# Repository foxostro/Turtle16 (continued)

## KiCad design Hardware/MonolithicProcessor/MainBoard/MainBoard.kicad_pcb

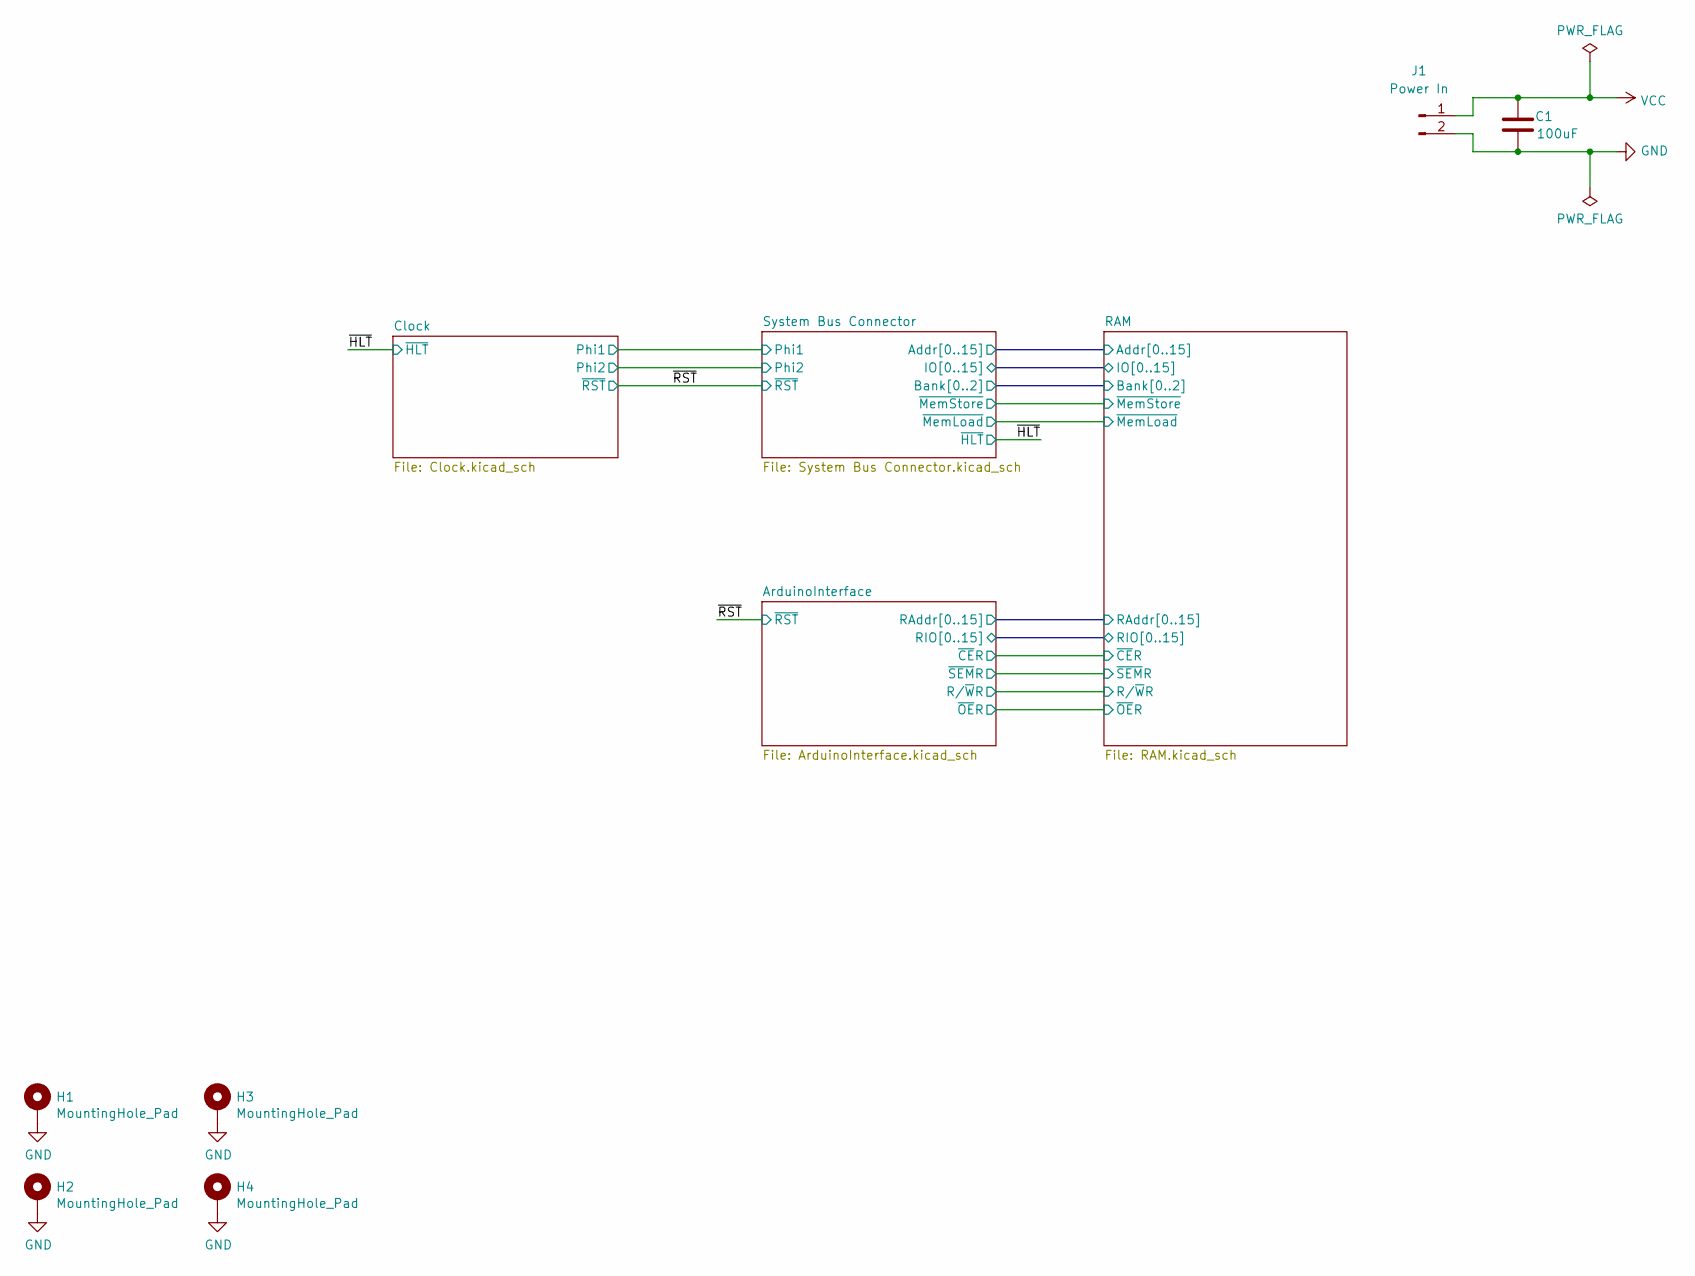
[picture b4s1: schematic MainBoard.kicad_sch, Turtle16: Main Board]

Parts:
C1: 100uF; C_1206_3216Metric; Manufacturer# AMK316ABJ107ML-T; Mouser# 963-AMK316ABJ107ML-T
H1, H2, H3, H4: MountingHole_Pad; MountingHole_3.2mm_M3_Pad
J1: Power In; 172448-0002; Manufacturer# 172448-0002; Mouser# 538-172448-0002

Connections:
GND: C1.2, H1.1, H2.1, H3.1, H4.1, J1.2; also elsewhere on the board
VCC: C1.1, J1.1; also elsewhere on the board

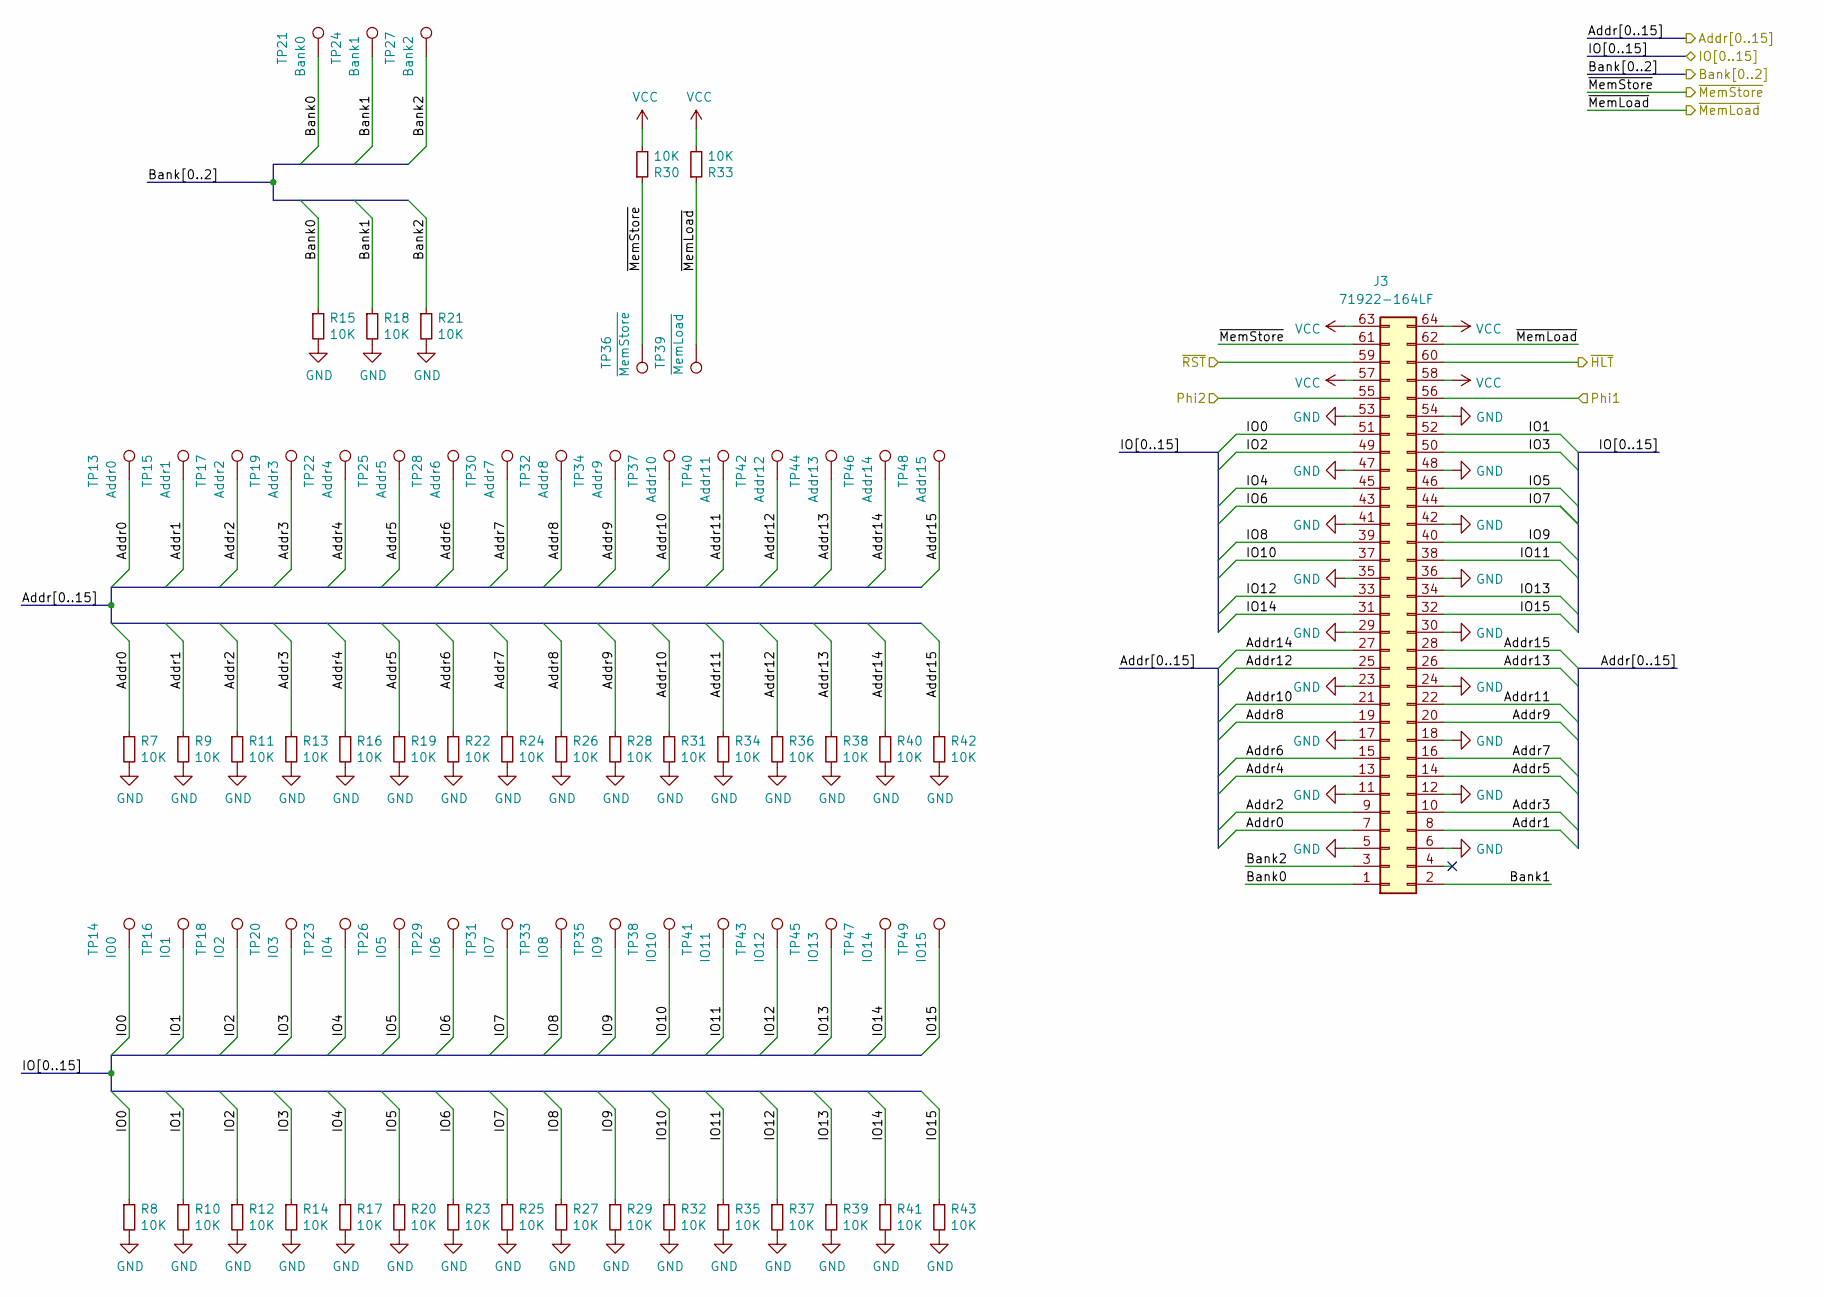
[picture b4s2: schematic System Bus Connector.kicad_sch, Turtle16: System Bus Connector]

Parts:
J3: 71922-164LF; IDC-Header_2x32_P2.54mm_Horizontal; Manufacturer# 71922-164LF; Mouser# 649-71922-164LF
R7, R8, R9, R10, R11, R12, R13, R14, R15, R16, R17, R18, R19, R20, R21, R22, R23, R24, R25, R26, R27, R28, R29, R30, R31, R32, R33, R34, R35, R36, R37, R38, R39, R40, R41, R42, R43: 10K; R_0603_1608Metric; Manufacturer# CR0603-FX-1002ELF; Mouser# 652-CR0603FX-1002ELF
TP13: Addr0; TestPoint_Pad_D1.0mm
TP14: IO0; TestPoint_Pad_D1.0mm
TP15: Addr1; TestPoint_Pad_D1.0mm
TP16: IO1; TestPoint_Pad_D1.0mm
TP17: Addr2; TestPoint_Pad_D1.0mm
TP18: IO2; TestPoint_Pad_D1.0mm
TP19: Addr3; TestPoint_Pad_D1.0mm
TP20: IO3; TestPoint_Pad_D1.0mm
TP21: Bank0; TestPoint_Pad_D1.0mm
TP22: Addr4; TestPoint_Pad_D1.0mm
TP23: IO4; TestPoint_Pad_D1.0mm
TP24: Bank1; TestPoint_Pad_D1.0mm
TP25: Addr5; TestPoint_Pad_D1.0mm
TP26: IO5; TestPoint_Pad_D1.0mm
TP27: Bank2; TestPoint_Pad_D1.0mm
TP28: Addr6; TestPoint_Pad_D1.0mm
TP29: IO6; TestPoint_Pad_D1.0mm
TP30: Addr7; TestPoint_Pad_D1.0mm
TP31: IO7; TestPoint_Pad_D1.0mm
TP32: Addr8; TestPoint_Pad_D1.0mm
TP33: IO8; TestPoint_Pad_D1.0mm
TP34: Addr9; TestPoint_Pad_D1.0mm
TP35: IO9; TestPoint_Pad_D1.0mm
TP36: ~{MemStore}; TestPoint_Pad_D1.0mm
TP37: Addr10; TestPoint_Pad_D1.0mm
TP38: IO10; TestPoint_Pad_D1.0mm
TP39: ~{MemLoad}; TestPoint_Pad_D1.0mm
TP40: Addr11; TestPoint_Pad_D1.0mm
TP41: IO11; TestPoint_Pad_D1.0mm
TP42: Addr12; TestPoint_Pad_D1.0mm
TP43: IO12; TestPoint_Pad_D1.0mm
TP44: Addr13; TestPoint_Pad_D1.0mm
TP45: IO13; TestPoint_Pad_D1.0mm
TP46: Addr14; TestPoint_Pad_D1.0mm
TP47: IO14; TestPoint_Pad_D1.0mm
TP48: Addr15; TestPoint_Pad_D1.0mm
TP49: IO15; TestPoint_Pad_D1.0mm

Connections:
/Clock/Phi1: J3.56; also elsewhere on the board
/Clock/Phi2: J3.55; also elsewhere on the board
/RAM/Addr0: J3.7, R7.1, TP13.1; also elsewhere on the board
/RAM/Addr1: J3.8, R9.1, TP15.1; also elsewhere on the board
/RAM/Addr2: J3.9, R11.1, TP17.1; also elsewhere on the board
/RAM/Addr3: J3.10, R13.1, TP19.1; also elsewhere on the board
/RAM/Addr4: J3.13, R16.1, TP22.1; also elsewhere on the board
/RAM/Addr5: J3.14, R19.1, TP25.1; also elsewhere on the board
/RAM/Addr6: J3.15, R22.1, TP28.1; also elsewhere on the board
/RAM/Addr7: J3.16, R24.1, TP30.1; also elsewhere on the board
/RAM/Addr8: J3.19, R26.1, TP32.1; also elsewhere on the board
/RAM/Addr9: J3.20, R28.1, TP34.1; also elsewhere on the board
/RAM/Addr10: J3.21, R31.1, TP37.1; also elsewhere on the board
/RAM/Addr11: J3.22, R34.1, TP40.1; also elsewhere on the board
/RAM/Addr12: J3.25, R36.1, TP42.1; also elsewhere on the board
/RAM/Addr13: J3.26, R38.1, TP44.1; also elsewhere on the board
/RAM/Addr14: J3.27, R40.1, TP46.1; also elsewhere on the board
/RAM/Addr15: J3.28, R42.1, TP48.1; also elsewhere on the board
/RAM/Bank0: J3.1, R15.1, TP21.1; also elsewhere on the board
/RAM/Bank1: J3.2, R18.1, TP24.1; also elsewhere on the board
/RAM/Bank2: J3.3, R21.1, TP27.1; also elsewhere on the board
/RAM/IO0: J3.51, R8.1, TP14.1; also elsewhere on the board
/RAM/IO1: J3.52, R10.1, TP16.1; also elsewhere on the board
/RAM/IO2: J3.49, R12.1, TP18.1; also elsewhere on the board
/RAM/IO3: J3.50, R14.1, TP20.1; also elsewhere on the board
/RAM/IO4: J3.45, R17.1, TP23.1; also elsewhere on the board
/RAM/IO5: J3.46, R20.1, TP26.1; also elsewhere on the board
/RAM/IO6: J3.43, R23.1, TP29.1; also elsewhere on the board
/RAM/IO7: J3.44, R25.1, TP31.1; also elsewhere on the board
/RAM/IO8: J3.39, R27.1, TP33.1; also elsewhere on the board
/RAM/IO9: J3.40, R29.1, TP35.1; also elsewhere on the board
/RAM/IO10: J3.37, R32.1, TP38.1; also elsewhere on the board
/RAM/IO11: J3.38, R35.1, TP41.1; also elsewhere on the board
/RAM/IO12: J3.33, R37.1, TP43.1; also elsewhere on the board
/RAM/IO13: J3.34, R39.1, TP45.1; also elsewhere on the board
/RAM/IO14: J3.31, R41.1, TP47.1; also elsewhere on the board
/RAM/IO15: J3.32, R43.1, TP49.1; also elsewhere on the board
/RAM/~MemLoad: J3.62, R33.1, TP39.1; also elsewhere on the board
/RAM/~MemStore: J3.61, R30.1, TP36.1; also elsewhere on the board
/~HLT: J3.60; also elsewhere on the board
/~RST: J3.59; also elsewhere on the board
GND: J3.5, J3.6, J3.11, J3.12, J3.17, J3.18, J3.23, J3.24, J3.29, J3.30, J3.35, J3.36, J3.41, J3.42, J3.47, J3.48, J3.53, J3.54, R7.2, R8.2, R9.2, R10.2, R11.2, R12.2, R13.2, R14.2, R15.2, R16.2, R17.2, R18.2, R19.2, R20.2, R21.2, R22.2, R23.2, R24.2, R25.2, R26.2, R27.2, R28.2, R29.2, R31.2, R32.2, R34.2, R35.2, R36.2, R37.2, R38.2, R39.2, R40.2, R41.2, R42.2, R43.2; also elsewhere on the board
VCC: J3.57, J3.58, J3.63, J3.64, R30.2, R33.2; also elsewhere on the board

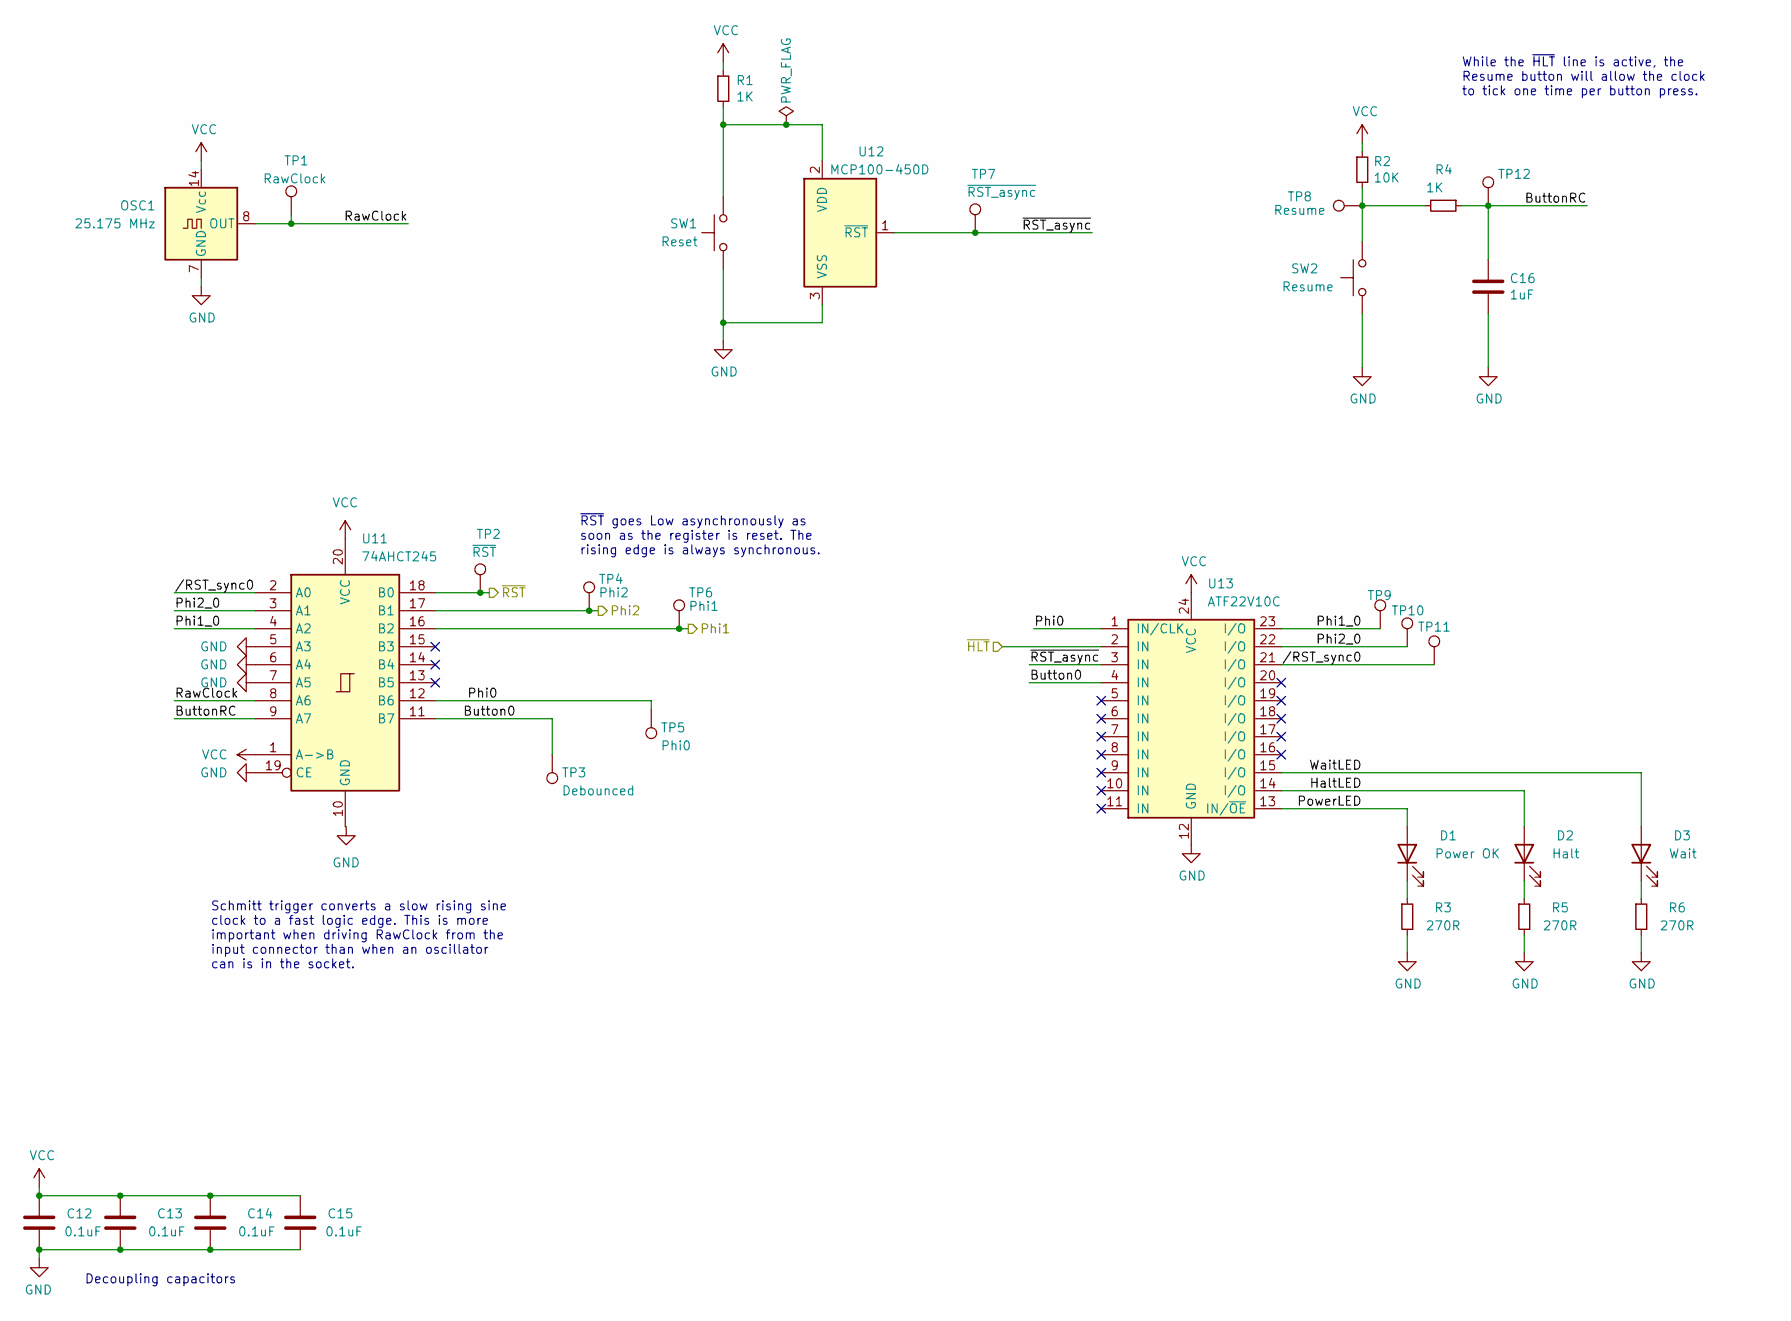
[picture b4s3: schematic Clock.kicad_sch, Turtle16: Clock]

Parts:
C12, C13, C14, C15: 0.1uF; C_0603_1608Metric; Manufacturer# EMK107B7104KAHT; Mouser# 963-EMK107B7104KAHT
C16: 1uF; C_0603_1608Metric; Manufacturer# CR0603-FX-2700ELF; Mouser# 652-CR0603FX-2700ELF
D1: Power OK; LED_0805_2012Metric; Manufacturer# AP2012ID; Mouser# 604-AP2012ID
D2: Halt; LED_0805_2012Metric; Manufacturer# AP2012ID; Mouser# 604-AP2012ID
D3: Wait; LED_0805_2012Metric; Manufacturer# AP2012ID; Mouser# 604-AP2012ID
OSC1: 25.175 MHz; Oscillator_DIP-14; Manufacturer# 1107741; Mouser# 535-1107741
R1: 1K; R_0603_1608Metric; Manufacturer# CR0603-FX-1002ELF; Mouser# 652-CR0603FX-1002ELF
R2: 10K; R_0603_1608Metric; Manufacturer# CR0603-FX-1002ELF; Mouser# 652-CR0603FX-1002ELF
R3, R5, R6: 270R; R_0603_1608Metric; Manufacturer# CR0603-FX-2700ELF; Mouser# 652-CR0603FX-2700ELF
R4: 1K; R_0603_1608Metric; Manufacturer# CR0603-FX-1001ELF; Mouser# 652-CR0603FX-1001ELF
SW1: Reset; SW_PUSH_6mm_H5mm
SW2: Resume; SW_PUSH_6mm_H5mm
TP1: RawClock; TestPoint_Pad_D1.0mm
TP2: ~{RST}; TestPoint_Pad_D1.0mm
TP3: Debounced; TestPoint_Pad_D1.0mm
TP4: Phi2; TestPoint_Pad_D1.0mm
TP5: Phi0; TestPoint_Pad_D1.0mm
TP6: Phi1; TestPoint_Pad_D1.0mm
TP7: ~{RST_async}; TestPoint_Pad_D1.0mm
TP8: Resume; TestPoint_Pad_D1.0mm
TP9: TestPoint_Pad_D1.0mm
TP10, TP11, TP12: TP; TestPoint_Pad_D1.0mm
U11: 74AHCT245; TSSOP-20_4.4x6.5mm_P0.65mm; Manufacturer# SN74AHCT245PWR; Mouser# 595-SN74AHCT245PWR
U12: MCP100-450D; TO-92; Manufacturer# MCP100-450DI/TO; Mouser# 579-MCP100-450DI/TO
U13: ATF22V10C; DIP-24_W7.62mm_Socket; Manufacturer# ATF22V10C-7PX; Mouser# 556-AF22V10C7PX

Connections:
/Clock/Button0: TP3.1, U11.11 (B7), U13.4 (IN)
/Clock/ButtonRC: C16.1, R4.1, TP12.1, U11.9 (A7)
/Clock/HaltLED: D2.2 (A), U13.14 (I/O)
/Clock/Phi0: TP5.1, U11.12 (B6), U13.1 (IN/CLK)
/Clock/Phi1: TP6.1, U11.16 (B2); also elsewhere on the board
/Clock/Phi1_0: TP9.1, U11.4 (A2), U13.23 (I/O)
/Clock/Phi2: TP4.1, U11.17 (B1); also elsewhere on the board
/Clock/Phi2_0: TP10.1, U11.3 (A1), U13.22 (I/O)
/Clock/PowerLED: D1.2 (A), U13.13 (IN/~OE)
/Clock/RawClock: OSC1.8 (OUT), TP1.1, U11.8 (A6)
/Clock/WaitLED: D3.2 (A), U13.15 (I/O)
/Clock//RST_sync0: TP11.1, U11.2 (A0), U13.21 (I/O)
/Clock/~RST_async: TP7.1, U12.1 (~RST), U13.3 (IN)
/~HLT: U13.2 (IN); also elsewhere on the board
/~RST: TP2.1, U11.18 (B0); also elsewhere on the board
GND: C12.2, C13.2, C14.2, C15.2, C16.2, OSC1.7 (GND), R3.2, R5.2, R6.2, SW1.1, SW2.1, U11.5 (A3), U11.6 (A4), U11.7 (A5), U11.10 (GND), U11.19 (CE), U12.3 (VSS), U13.12 (GND); also elsewhere on the board
unnamed: D1.1 (K), R3.1
unnamed: D2.1 (K), R5.1
unnamed: D3.1 (K), R6.1
unnamed: R2.2, R4.2, SW2.2, TP8.1
unnamed: R1.2, SW1.2, U12.2 (VDD)
VCC: C12.1, C13.1, C14.1, C15.1, OSC1.14 (Vcc), R1.1, R2.1, U11.1 (A->B), U11.20 (VCC), U13.24 (VCC); also elsewhere on the board

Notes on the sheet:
~{RST} goes Low asynchronously as soon as the register is reset. The rising edge is always synchronous.
Schmitt trigger converts a slow rising sine clock to a fast logic edge. This is more important when driving RawClock from the input connector than when an oscillator can is in the socket.
While the ~{HLT} line is active, the Resume button will allow the clock to tick one time per button press.
Decoupling capacitors

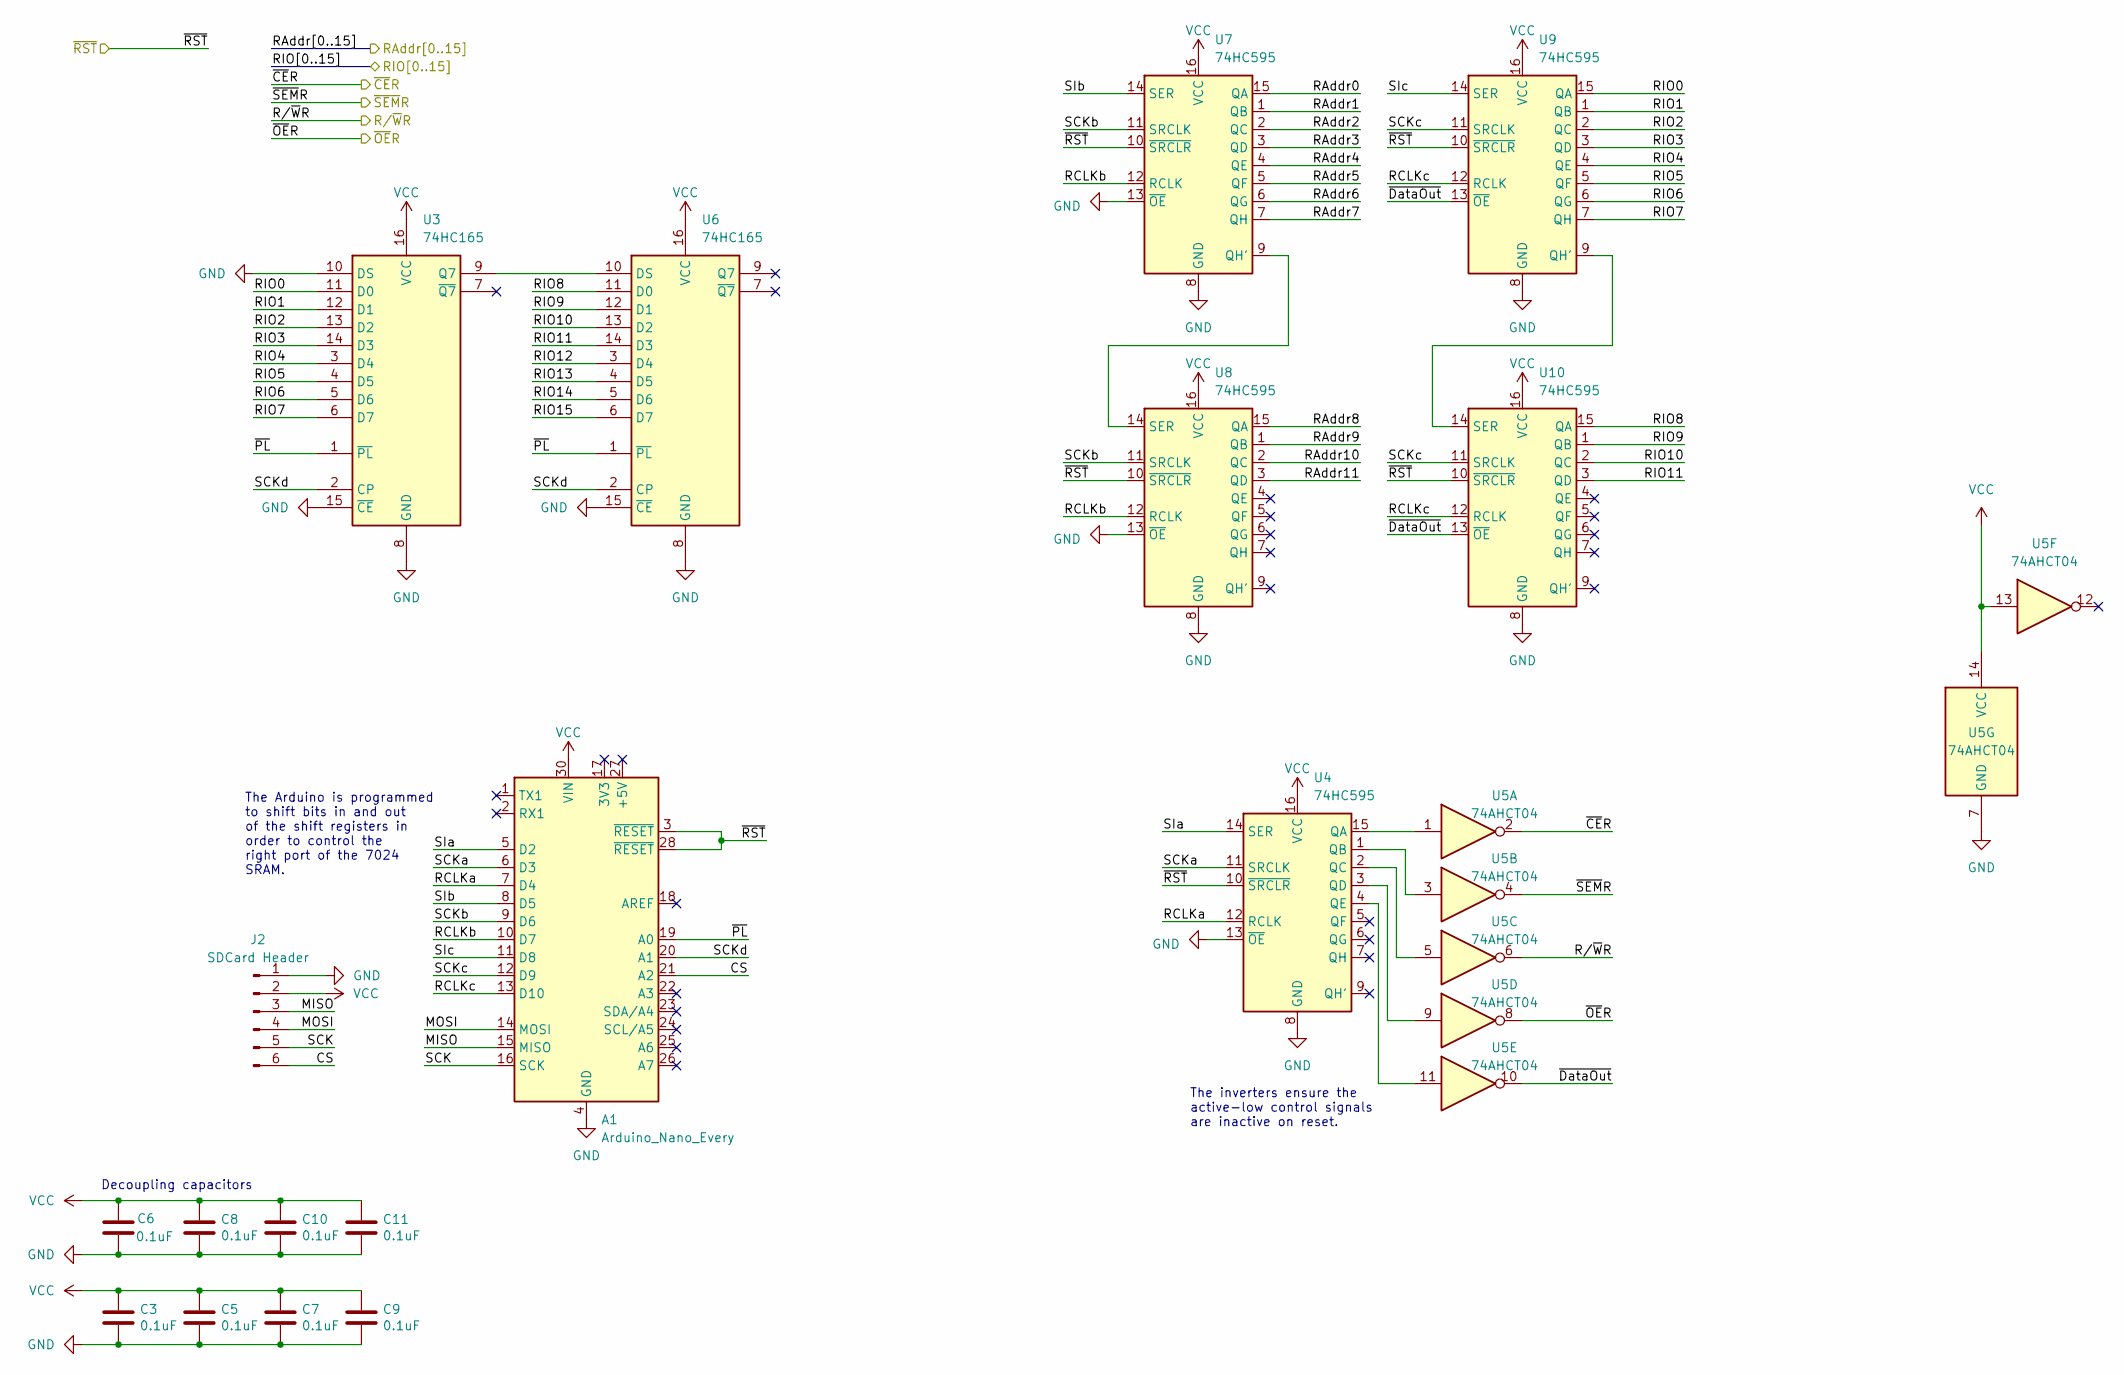
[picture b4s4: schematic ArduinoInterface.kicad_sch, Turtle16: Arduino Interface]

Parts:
A1: Arduino_Nano_Every; Arduino_Nano
C3, C5, C6, C7, C8, C9, C10, C11: 0.1uF; C_0603_1608Metric; Manufacturer# EMK107B7104KAHT; Mouser# 963-EMK107B7104KAHT
J2: SDCard Header; PinHeader_1x06_P2.54mm_Vertical
U3, U6: 74HC165; TSSOP-16_4.4x5mm_P0.65mm; Manufacturer# 74HC165PW-Q100,118; Mouser# 771-74HC165PWQ100118
U4, U7, U8, U9, U10: 74HC595; TSSOP-16_4.4x5mm_P0.65mm; Manufacturer# 74HC595PW-Q100,118; Mouser# 771-74HC595PW-Q100
U5: 74AHCT04; TSSOP-14_4.4x5mm_P0.65mm; Manufacturer# 74AHCT04APWJ; Mouser# 771-74AHCT04APWJ

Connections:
/ArduinoInterface/CS: A1.21 (A2), J2.6
/ArduinoInterface/MISO: A1.15 (MISO), J2.3
/ArduinoInterface/MOSI: A1.14 (MOSI), J2.4
/ArduinoInterface/RAddr0: U7.15 (QA); also elsewhere on the board
/ArduinoInterface/RAddr1: U7.1 (QB); also elsewhere on the board
/ArduinoInterface/RAddr2: U7.2 (QC); also elsewhere on the board
/ArduinoInterface/RAddr3: U7.3 (QD); also elsewhere on the board
/ArduinoInterface/RAddr4: U7.4 (QE); also elsewhere on the board
/ArduinoInterface/RAddr5: U7.5 (QF); also elsewhere on the board
/ArduinoInterface/RAddr6: U7.6 (QG); also elsewhere on the board
/ArduinoInterface/RAddr7: U7.7 (QH); also elsewhere on the board
/ArduinoInterface/RAddr8: U8.15 (QA); also elsewhere on the board
/ArduinoInterface/RAddr9: U8.1 (QB); also elsewhere on the board
/ArduinoInterface/RAddr10: U8.2 (QC); also elsewhere on the board
/ArduinoInterface/RAddr11: U8.3 (QD); also elsewhere on the board
/ArduinoInterface/RCLKa: A1.7 (D4), U4.12 (RCLK)
/ArduinoInterface/RCLKb: A1.10 (D7), U7.12 (RCLK), U8.12 (RCLK)
/ArduinoInterface/RCLKc: A1.13 (D10), U9.12 (RCLK), U10.12 (RCLK)
/ArduinoInterface/RIO0: U3.11 (D0), U9.15 (QA); also elsewhere on the board
/ArduinoInterface/RIO1: U3.12 (D1), U9.1 (QB); also elsewhere on the board
/ArduinoInterface/RIO2: U3.13 (D2), U9.2 (QC); also elsewhere on the board
/ArduinoInterface/RIO3: U3.14 (D3), U9.3 (QD); also elsewhere on the board
/ArduinoInterface/RIO4: U3.3 (D4), U9.4 (QE); also elsewhere on the board
/ArduinoInterface/RIO5: U3.4 (D5), U9.5 (QF); also elsewhere on the board
/ArduinoInterface/RIO6: U3.5 (D6), U9.6 (QG); also elsewhere on the board
/ArduinoInterface/RIO7: U3.6 (D7), U9.7 (QH); also elsewhere on the board
/ArduinoInterface/RIO8: U6.11 (D0), U10.15 (QA); also elsewhere on the board
/ArduinoInterface/RIO9: U6.12 (D1), U10.1 (QB); also elsewhere on the board
/ArduinoInterface/RIO10: U6.13 (D2), U10.2 (QC); also elsewhere on the board
/ArduinoInterface/RIO11: U6.14 (D3), U10.3 (QD); also elsewhere on the board
/ArduinoInterface/RIO12: U6.3 (D4); also elsewhere on the board
/ArduinoInterface/RIO13: U6.4 (D5); also elsewhere on the board
/ArduinoInterface/RIO14: U6.5 (D6); also elsewhere on the board
/ArduinoInterface/RIO15: U6.6 (D7); also elsewhere on the board
/ArduinoInterface/R/~WR: U5.6; also elsewhere on the board
/ArduinoInterface/SCK: A1.16 (SCK), J2.5
/ArduinoInterface/SCKa: A1.6 (D3), U4.11 (SRCLK)
/ArduinoInterface/SCKb: A1.9 (D6), U7.11 (SRCLK), U8.11 (SRCLK)
/ArduinoInterface/SCKc: A1.12 (D9), U9.11 (SRCLK), U10.11 (SRCLK)
/ArduinoInterface/SCKd: A1.20 (A1), U3.2 (CP), U6.2 (CP)
/ArduinoInterface/SIa: A1.5 (D2), U4.14 (SER)
/ArduinoInterface/SIb: A1.8 (D5), U7.14 (SER)
/ArduinoInterface/SIc: A1.11 (D8), U9.14 (SER)
/ArduinoInterface/~CER: U5.2; also elsewhere on the board
/ArduinoInterface/~DataOut: U5.10, U9.13 (~OE), U10.13 (~OE)
/ArduinoInterface/~OER: U5.8; also elsewhere on the board
/ArduinoInterface/~PL: A1.19 (A0), U3.1 (~PL), U6.1 (~PL)
/ArduinoInterface/~SEMR: U5.4; also elsewhere on the board
/~RST: A1.3 (~RESET), A1.28 (~RESET), U4.10 (~SRCLR), U7.10 (~SRCLR), U8.10 (~SRCLR), U9.10 (~SRCLR), U10.10 (~SRCLR); also elsewhere on the board
GND: A1.4 (GND), A1.29 (GND), C3.2, C5.2, C6.2, C7.2, C8.2, C9.2, C10.2, C11.2, J2.1, U3.8 (GND), U3.10 (DS), U3.15 (~CE), U4.8 (GND), U4.13 (~OE), U5.7 (GND), U6.8 (GND), U6.15 (~CE), U7.8 (GND), U7.13 (~OE), U8.8 (GND), U8.13 (~OE), U9.8 (GND), U10.8 (GND); also elsewhere on the board
unnamed: U3.9 (Q7), U6.10 (DS)
unnamed: U4.15 (QA), U5.1
unnamed: U4.1 (QB), U5.3
unnamed: U4.2 (QC), U5.5
unnamed: U4.3 (QD), U5.9
unnamed: U4.4 (QE), U5.11
unnamed: U7.9 (QH'), U8.14 (SER)
unnamed: U9.9 (QH'), U10.14 (SER)
VCC: A1.30 (VIN), C3.1, C5.1, C6.1, C7.1, C8.1, C9.1, C10.1, C11.1, J2.2, U3.16 (VCC), U4.16 (VCC), U5.13, U5.14 (VCC), U6.16 (VCC), U7.16 (VCC), U8.16 (VCC), U9.16 (VCC), U10.16 (VCC); also elsewhere on the board

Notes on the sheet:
Decoupling capacitors
The Arduino is programmed to shift bits in and out of the shift registers in order to control the right port of the 7024 SRAM.
The inverters ensure the active-low control signals are inactive on reset.

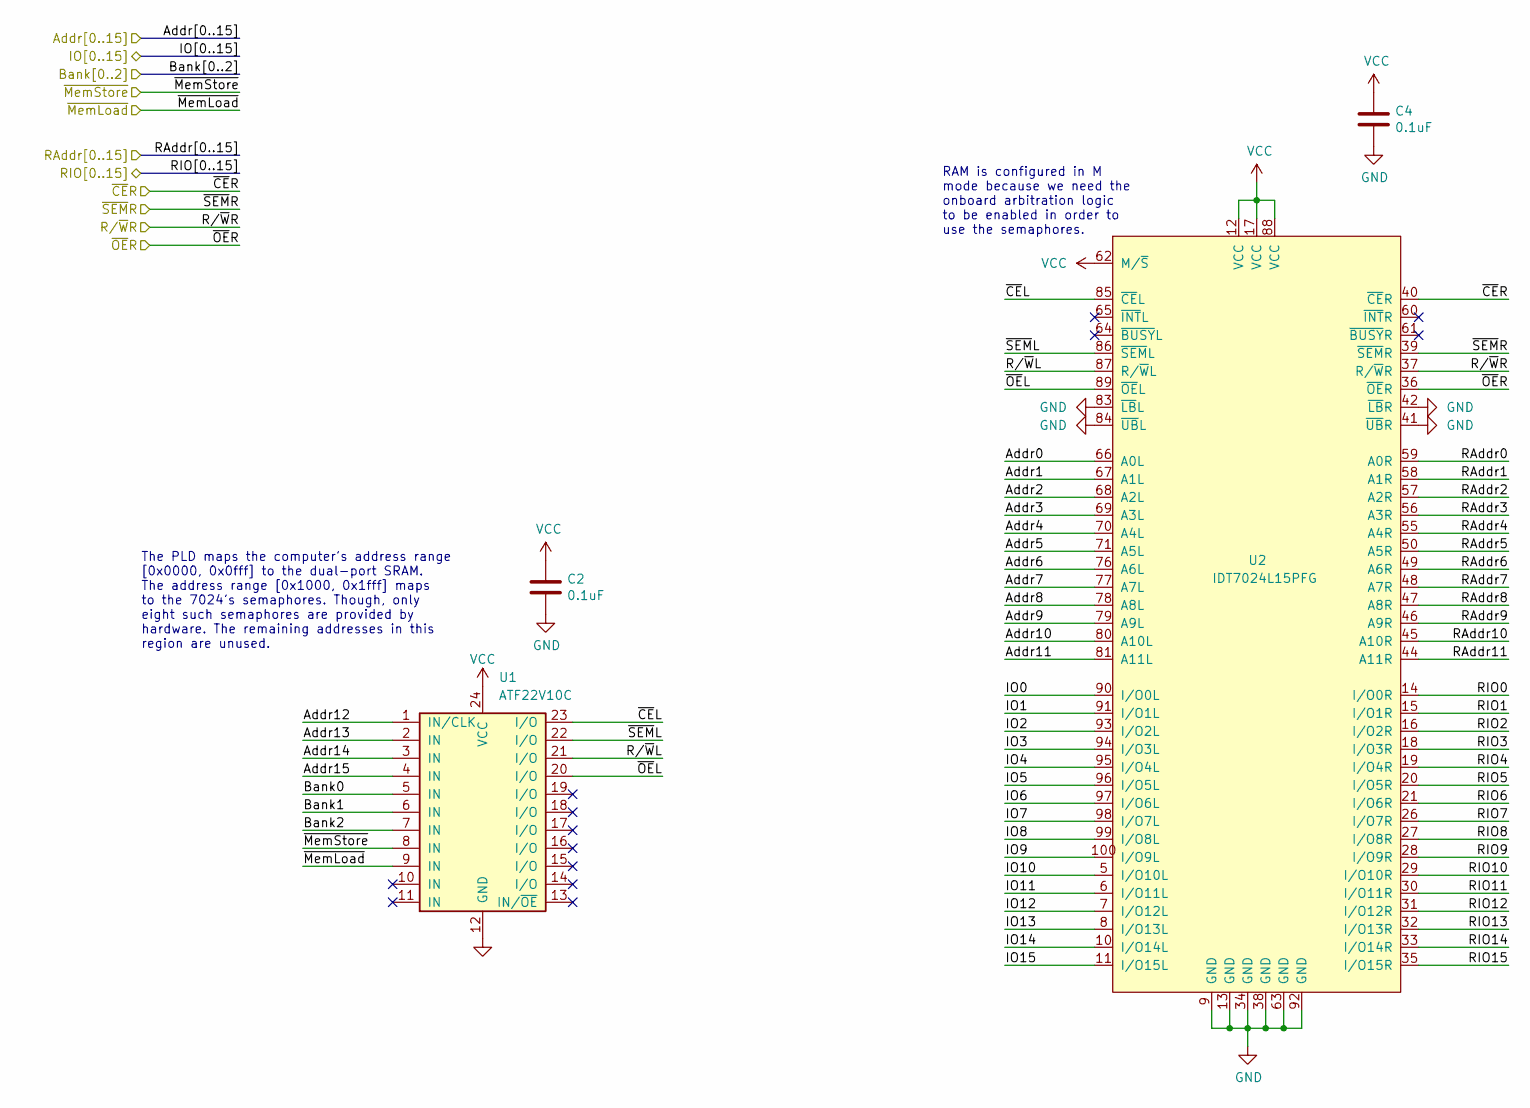
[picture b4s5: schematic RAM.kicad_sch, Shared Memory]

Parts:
C2, C4: 0.1uF; C_0603_1608Metric; Manufacturer# EMK107B7104KAHT; Mouser# 963-EMK107B7104KAHT
U1: ATF22V10C; DIP-24_W7.62mm_Socket; Manufacturer# ATF22V10C-7PX; Mouser# 556-AF22V10C7PX
U2: IDT7024L15PFG; TQFP-100_14x14mm_P0.5mm; Manufacturer# 7024L15PFG; Mouser# 972-7024L15PFG

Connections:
/ArduinoInterface/RAddr0: U2.59 (A0R); also elsewhere on the board
/ArduinoInterface/RAddr1: U2.58 (A1R); also elsewhere on the board
/ArduinoInterface/RAddr2: U2.57 (A2R); also elsewhere on the board
/ArduinoInterface/RAddr3: U2.56 (A3R); also elsewhere on the board
/ArduinoInterface/RAddr4: U2.55 (A4R); also elsewhere on the board
/ArduinoInterface/RAddr5: U2.50 (A5R); also elsewhere on the board
/ArduinoInterface/RAddr6: U2.49 (A6R); also elsewhere on the board
/ArduinoInterface/RAddr7: U2.48 (A7R); also elsewhere on the board
/ArduinoInterface/RAddr8: U2.47 (A8R); also elsewhere on the board
/ArduinoInterface/RAddr9: U2.46 (A9R); also elsewhere on the board
/ArduinoInterface/RAddr10: U2.45 (A10R); also elsewhere on the board
/ArduinoInterface/RAddr11: U2.44 (A11R); also elsewhere on the board
/ArduinoInterface/RIO0: U2.14 (I/O0R); also elsewhere on the board
/ArduinoInterface/RIO1: U2.15 (I/O1R); also elsewhere on the board
/ArduinoInterface/RIO2: U2.16 (I/O2R); also elsewhere on the board
/ArduinoInterface/RIO3: U2.18 (I/O3R); also elsewhere on the board
/ArduinoInterface/RIO4: U2.19 (I/O4R); also elsewhere on the board
/ArduinoInterface/RIO5: U2.20 (I/O5R); also elsewhere on the board
/ArduinoInterface/RIO6: U2.21 (I/O6R); also elsewhere on the board
/ArduinoInterface/RIO7: U2.26 (I/O7R); also elsewhere on the board
/ArduinoInterface/RIO8: U2.27 (I/O8R); also elsewhere on the board
/ArduinoInterface/RIO9: U2.28 (I/O9R); also elsewhere on the board
/ArduinoInterface/RIO10: U2.29 (I/O10R); also elsewhere on the board
/ArduinoInterface/RIO11: U2.30 (I/O11R); also elsewhere on the board
/ArduinoInterface/RIO12: U2.31 (I/O12R); also elsewhere on the board
/ArduinoInterface/RIO13: U2.32 (I/O13R); also elsewhere on the board
/ArduinoInterface/RIO14: U2.33 (I/O14R); also elsewhere on the board
/ArduinoInterface/RIO15: U2.35 (I/O15R); also elsewhere on the board
/ArduinoInterface/R/~WR: U2.37 (R/~WR); also elsewhere on the board
/ArduinoInterface/~CER: U2.40 (~CER); also elsewhere on the board
/ArduinoInterface/~OER: U2.36 (~OER); also elsewhere on the board
/ArduinoInterface/~SEMR: U2.39 (~SEMR); also elsewhere on the board
/RAM/Addr0: U2.66 (A0L); also elsewhere on the board
/RAM/Addr1: U2.67 (A1L); also elsewhere on the board
/RAM/Addr2: U2.68 (A2L); also elsewhere on the board
/RAM/Addr3: U2.69 (A3L); also elsewhere on the board
/RAM/Addr4: U2.70 (A4L); also elsewhere on the board
/RAM/Addr5: U2.71 (A5L); also elsewhere on the board
/RAM/Addr6: U2.76 (A6L); also elsewhere on the board
/RAM/Addr7: U2.77 (A7L); also elsewhere on the board
/RAM/Addr8: U2.78 (A8L); also elsewhere on the board
/RAM/Addr9: U2.79 (A9L); also elsewhere on the board
/RAM/Addr10: U2.80 (A10L); also elsewhere on the board
/RAM/Addr11: U2.81 (A11L); also elsewhere on the board
/RAM/Addr12: U1.1 (IN/CLK); also elsewhere on the board
/RAM/Addr13: U1.2 (IN); also elsewhere on the board
/RAM/Addr14: U1.3 (IN); also elsewhere on the board
/RAM/Addr15: U1.4 (IN); also elsewhere on the board
/RAM/Bank0: U1.5 (IN); also elsewhere on the board
/RAM/Bank1: U1.6 (IN); also elsewhere on the board
/RAM/Bank2: U1.7 (IN); also elsewhere on the board
/RAM/IO0: U2.90 (I/O0L); also elsewhere on the board
/RAM/IO1: U2.91 (I/O1L); also elsewhere on the board
/RAM/IO2: U2.93 (I/O2L); also elsewhere on the board
/RAM/IO3: U2.94 (I/O3L); also elsewhere on the board
/RAM/IO4: U2.95 (I/O4L); also elsewhere on the board
/RAM/IO5: U2.96 (I/O5L); also elsewhere on the board
/RAM/IO6: U2.97 (I/O6L); also elsewhere on the board
/RAM/IO7: U2.98 (I/O7L); also elsewhere on the board
/RAM/IO8: U2.99 (I/O8L); also elsewhere on the board
/RAM/IO9: U2.100 (I/O9L); also elsewhere on the board
/RAM/IO10: U2.5 (I/O10L); also elsewhere on the board
/RAM/IO11: U2.6 (I/O11L); also elsewhere on the board
/RAM/IO12: U2.7 (I/O12L); also elsewhere on the board
/RAM/IO13: U2.8 (I/O13L); also elsewhere on the board
/RAM/IO14: U2.10 (I/O14L); also elsewhere on the board
/RAM/IO15: U2.11 (I/O15L); also elsewhere on the board
/RAM/R/~WL: U1.21 (I/O), U2.87 (R/~WL)
/RAM/~CEL: U1.23 (I/O), U2.85 (~CEL)
/RAM/~MemLoad: U1.9 (IN); also elsewhere on the board
/RAM/~MemStore: U1.8 (IN); also elsewhere on the board
/RAM/~OEL: U1.20 (I/O), U2.89 (~OEL)
/RAM/~SEML: U1.22 (I/O), U2.86 (~SEML)
GND: C2.2, C4.2, U1.12 (GND), U2.9 (GND), U2.13 (GND), U2.34 (GND), U2.38 (GND), U2.41 (~UBR), U2.42 (~LBR), U2.63 (GND), U2.83 (~LBL), U2.84 (~UBL), U2.92 (GND); also elsewhere on the board
VCC: C2.1, C4.1, U1.24 (VCC), U2.12 (VCC), U2.17 (VCC), U2.62 (M/~S), U2.88 (VCC); also elsewhere on the board

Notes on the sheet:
The PLD maps the computer's address range [0x0000, 0x0fff] to the dual-port SRAM. The address range [0x1000, 0x1fff] maps to the 7024's semaphores. Though, only eight such semaphores are provided by hardware. The remaining addresses in this region are unused.
RAM is configured in M mode because we need the onboard arbitration logic to be enabled in order to use the semaphores.
